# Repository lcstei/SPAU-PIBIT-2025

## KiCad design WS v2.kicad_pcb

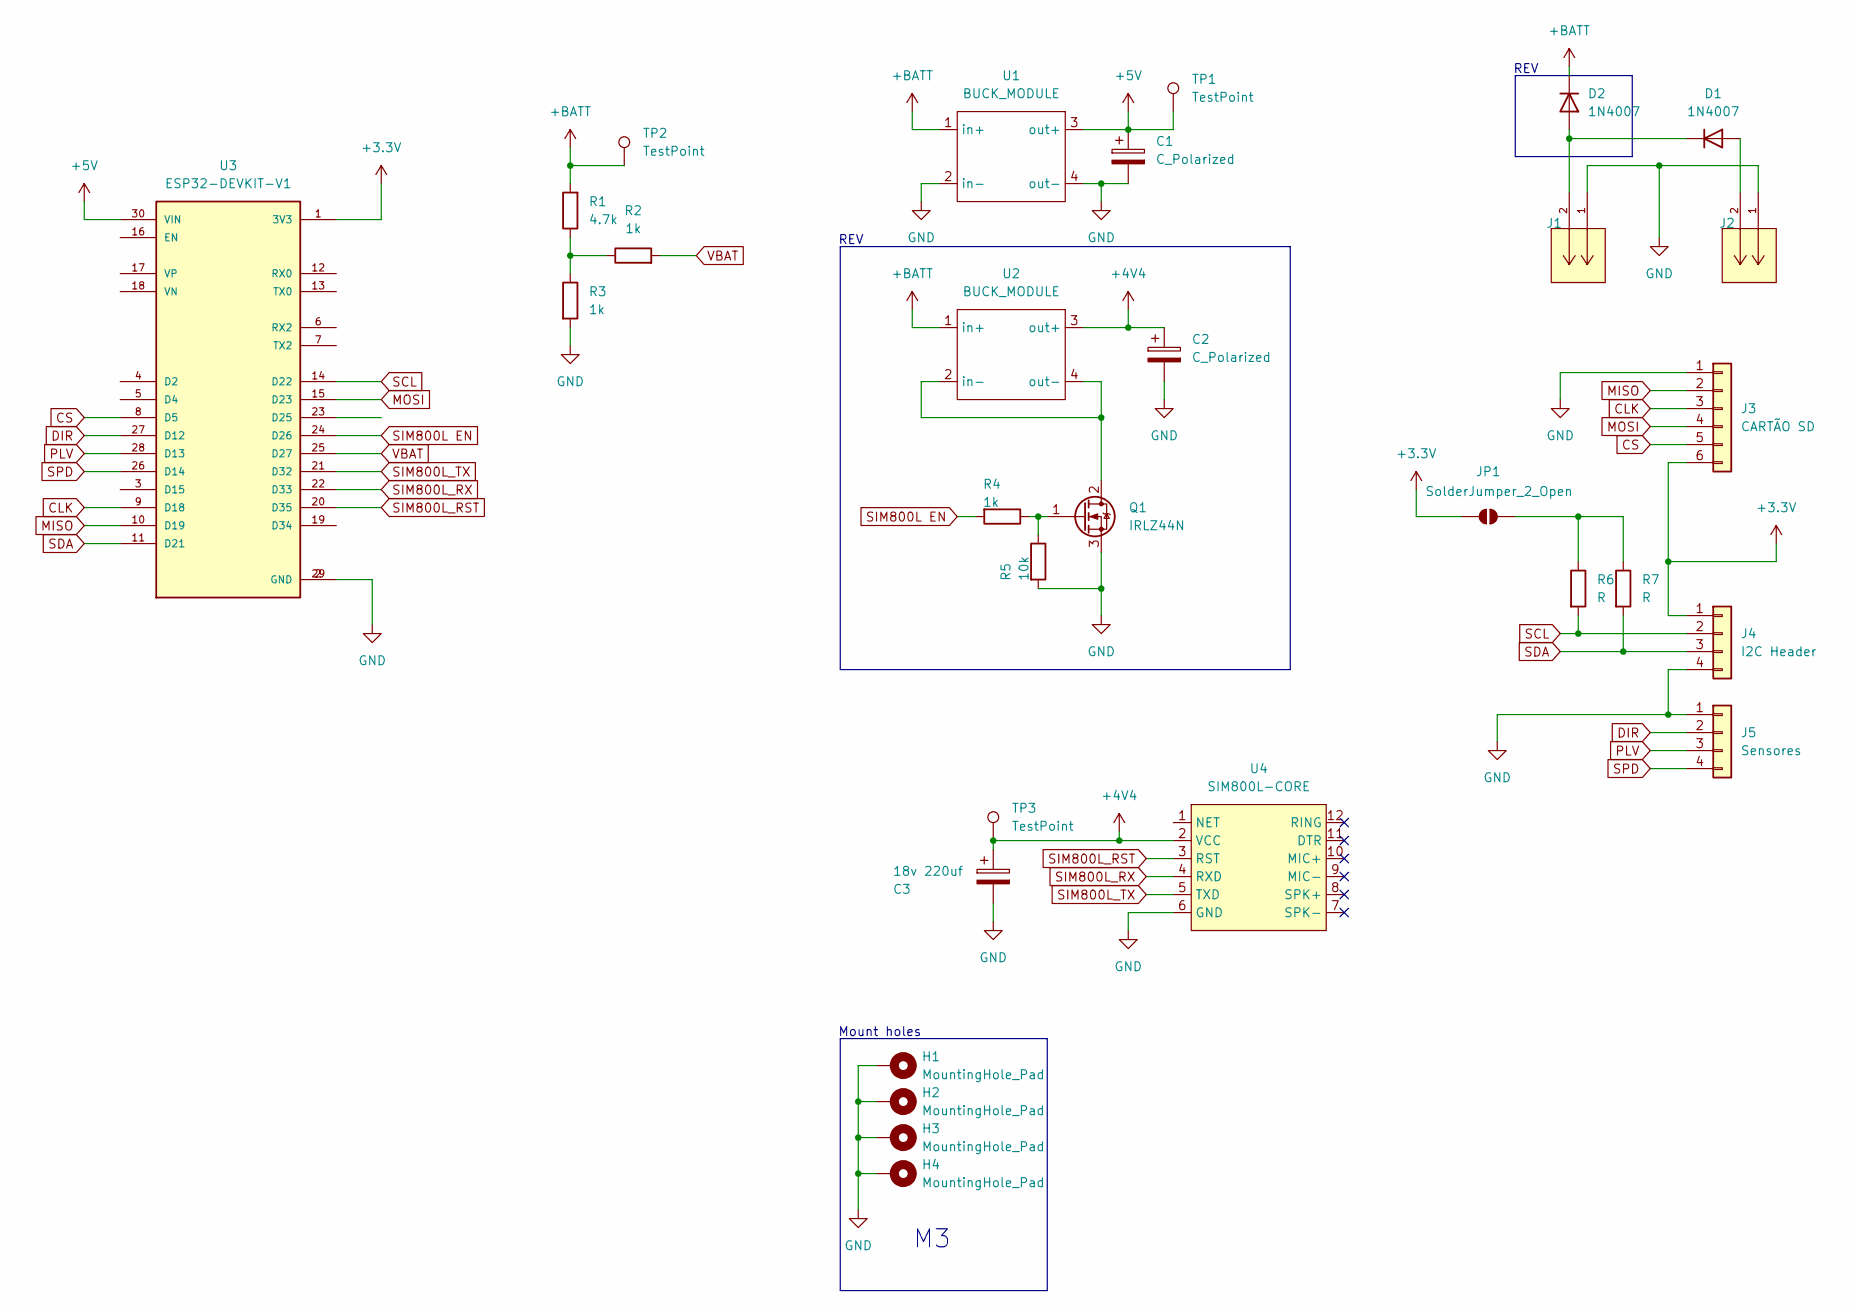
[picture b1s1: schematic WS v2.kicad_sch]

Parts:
C1, C2: C_Polarized; C_Disc_D4.7mm_W2.5mm_P5.00mm
C3: 18v 220uf; CP_Radial_D6.3mm_P2.50mm
D1, D2: 1N4007; D_DO-41_SOD81_P10.16mm_Horizontal
H1, H2, H3, H4: MountingHole_Pad; MountingHole_3.2mm_M3_Pad_TopBottom
J1, J2: 22053021; Molex_KK-254_AE-6410-02A_1x02_P2.54mm_Vertical; MANUFACTURER_PART_NUMBER 22053021
J3: CARTÃO SD; PinSocket_1x06_P2.54mm_Vertical
J4: I2C Header; Molex_KK-254_AE-6410-04A_1x04_P2.54mm_Vertical
J5: Sensores; Molex_KK-254_AE-6410-04A_1x04_P2.54mm_Vertical
JP1: SolderJumper_2_Open; SolderJumper-2_P1.3mm_Open_Pad1.0x1.5mm
Q1: IRLZ44N; TO-220-3_Vertical
R1: 4.7k; R_Axial_DIN0207_L6.3mm_D2.5mm_P7.62mm_Horizontal
R2, R3, R4: 1k; R_Axial_DIN0207_L6.3mm_D2.5mm_P7.62mm_Horizontal
R5: 10k; R_Axial_DIN0207_L6.3mm_D2.5mm_P7.62mm_Horizontal
R6, R7: R; R_Axial_DIN0207_L6.3mm_D2.5mm_P7.62mm_Horizontal
TP1, TP2, TP3: TestPoint; TestPoint_Pad_D2.0mm
U1, U2: BUCK_MODULE; BUCK lm2596 Modulo
U3: ESP32-DEVKIT-V1; MODULE_ESP32_DEVKIT_V1; PARTREV N/A
U4: SIM800L-CORE

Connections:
+3.3V: J3.6, J4.1, JP1.1 (A), U3.1 (3V3)
+4V4: C2.1, C3.1, TP3.1, U2.3 (out+), U4.2 (VCC)
+5V: C1.1, TP1.1, U1.3 (out+), U3.30 (VIN)
CLK: J3.3, U3.9 (D18)
CS: J3.5, U3.8 (D5)
DIR: J5.2, U3.27 (D12)
GND: C1.2, C2.2, C3.2, H1.1, H2.1, H3.1, H4.1, J1.1, J2.1, J3.1, J4.4, J5.1, Q1.3 (S), R3.2, R5.2, U1.2 (in-), U1.4 (out-), U3.2 (GND), U3.29 (GND), U4.6 (GND)
MISO: J3.2, U3.10 (D19)
MOSI: J3.4, U3.15 (D23)
unnamed: D1.2 (A), J2.2
unnamed: JP1.2 (B), R6.1, R7.1
unnamed: Q1.2 (D), U2.2 (in-), U2.4 (out-)
unnamed: Q1.1 (G), R4.1, R5.1
unnamed: R1.1, R2.1, R3.1
PLV: J5.3, U3.28 (D13)
SCL: J4.2, R6.2, U3.14 (D22)
SDA: J4.3, R7.2, U3.11 (D21)
SIM800L EN: R4.2, U3.24 (D26)
SIM800L_RST: U3.20 (D35), U4.3 (RST)
SIM800L_RX: U3.22 (D33), U4.4 (RXD)
SIM800L_TX: U3.21 (D32), U4.5 (TXD)
SPD: J5.4, U3.26 (D14)
VBAT: R2.2, U3.25 (D27)

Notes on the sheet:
REV
Mount holes

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
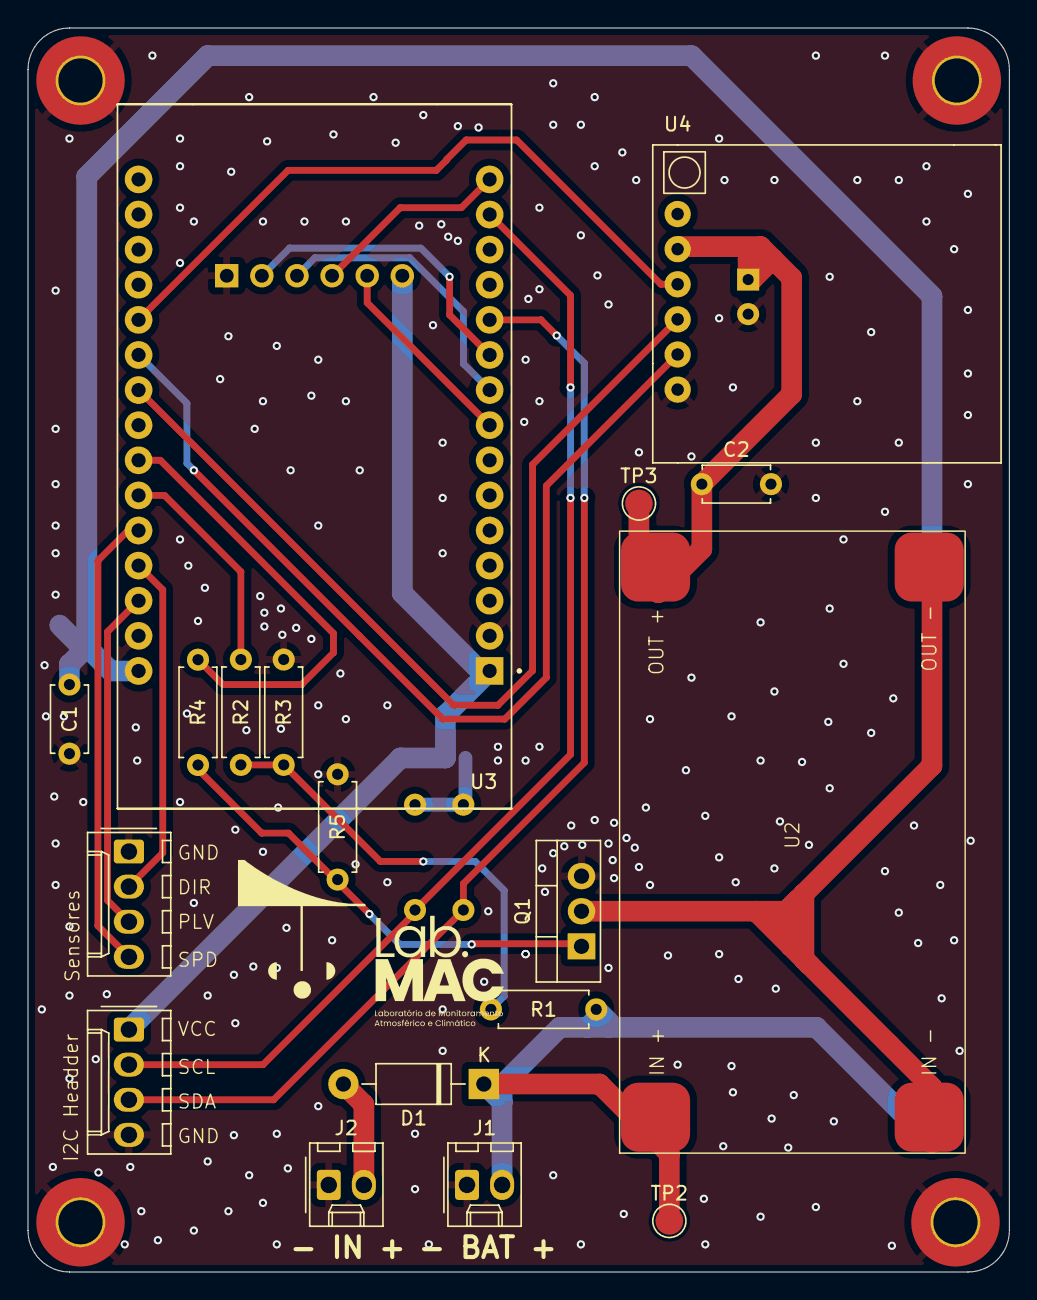
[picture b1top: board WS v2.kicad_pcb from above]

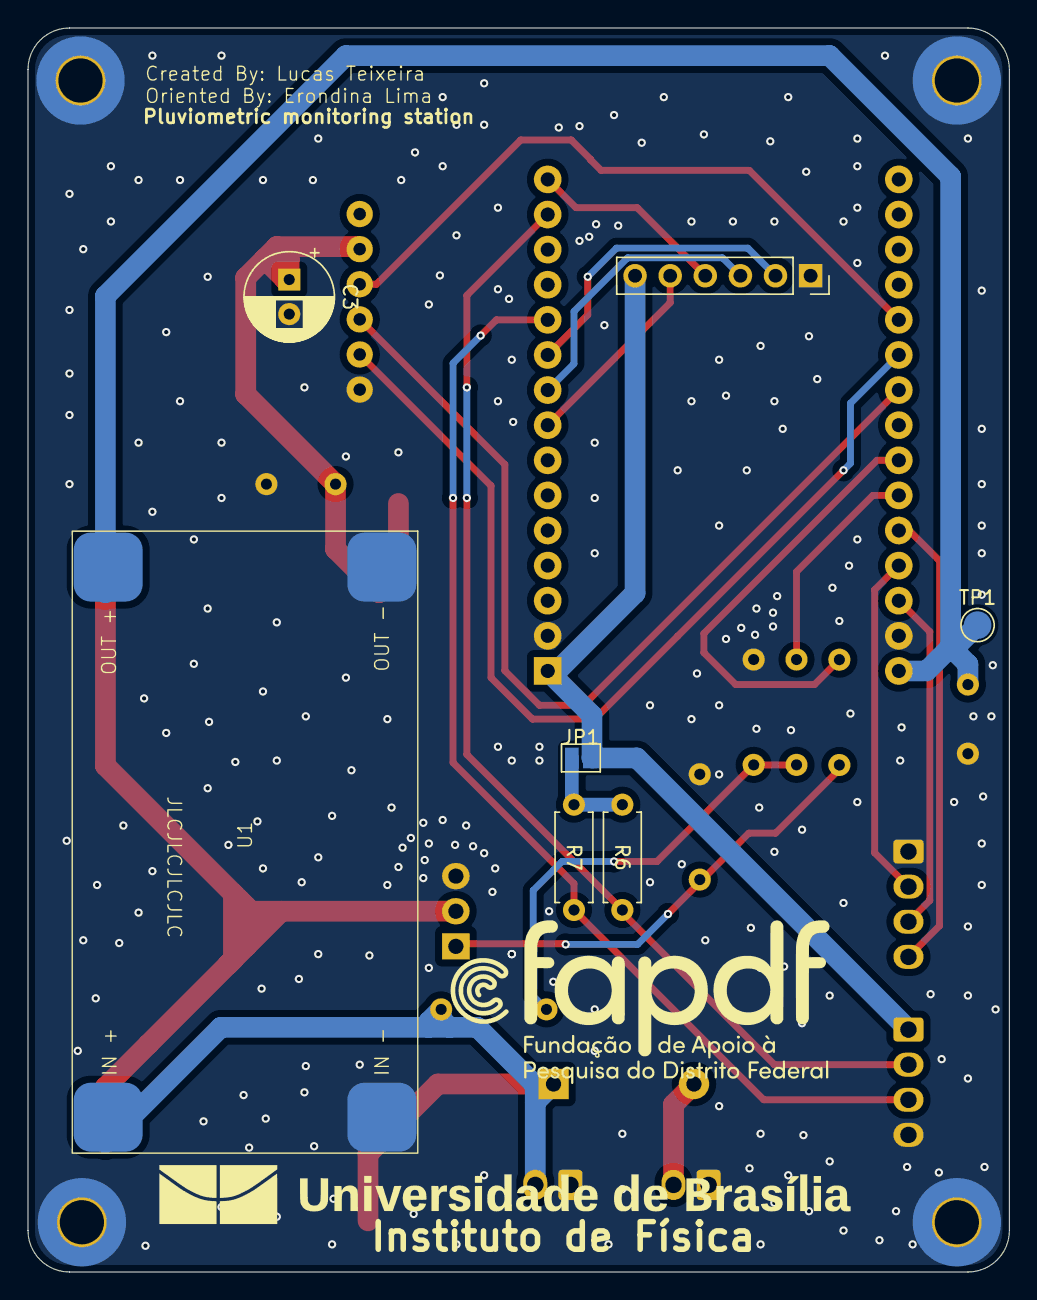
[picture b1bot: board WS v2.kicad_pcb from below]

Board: 2 copper layers, 71.0 x 90.0 mm, 29 parts (7 on the bottom side), 24 nets.

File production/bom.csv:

Designator,Footprint,Quantity,Value,LCSC Part #
"C1, C2",C_Disc_D4.7mm_W2.5mm_P5.00mm,2,C_Polarized,
C3,CP_Radial_D6.3mm_P2.50mm,1,18v 220uf,
D1,D_DO-41_SOD81_P10.16mm_Horizontal,1,1N4007,
"J1, J2",Molex_KK-254_AE-6410-02A_1x02_P2.54mm_Vertical,2,22053021,
J3,PinSocket_1x06_P2.54mm_Vertical,1,CARTÃO SD,
J4,Molex_KK-254_AE-6410-04A_1x04_P2.54mm_Vertical,1,I2C Header,
J5,Molex_KK-254_AE-6410-04A_1x04_P2.54mm_Vertical,1,Sensores,
Q1,TO-220-3_Vertical,1,IRLZ44N,
R1,R_Axial_DIN0207_L6.3mm_D2.5mm_P7.62mm_Horizontal,1,4.7k,
R2,R_Axial_DIN0207_L6.3mm_D2.5mm_P7.62mm_Horizontal,1,"1,5k",
R3,R_Axial_DIN0207_L6.3mm_D2.5mm_P7.62mm_Horizontal,1,100k,
R4,R_Axial_DIN0207_L6.3mm_D2.5mm_P7.62mm_Horizontal,1,1k,
R5,R_Axial_DIN0207_L6.3mm_D2.5mm_P7.62mm_Horizontal,1,10k,
"R6, R7",R_Axial_DIN0207_L6.3mm_D2.5mm_P7.62mm_Horizontal,2,R,
"TP1, TP2, TP3",TestPoint_Pad_D2.0mm,3,TestPoint,
"U1, U2",BUCK lm2596 Modulo,2,BUCK_MODULE,
U3,MODULE_ESP32_DEVKIT_V1,1,ESP32-DEVKIT-V1,
U4,SIM800L-CORE,1,SIM800L-CORE,

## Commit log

2025-09-25 First and Final COMMIT
    I HOPE SO
